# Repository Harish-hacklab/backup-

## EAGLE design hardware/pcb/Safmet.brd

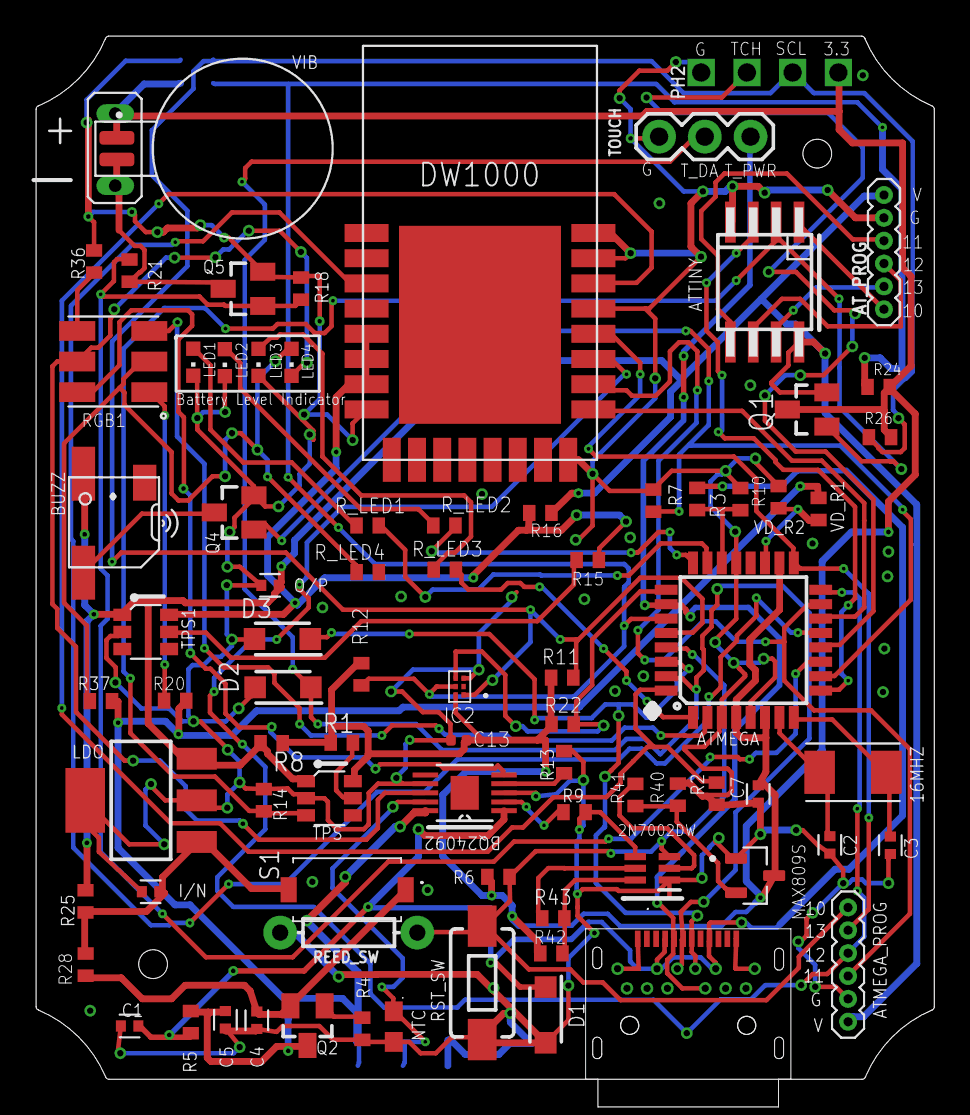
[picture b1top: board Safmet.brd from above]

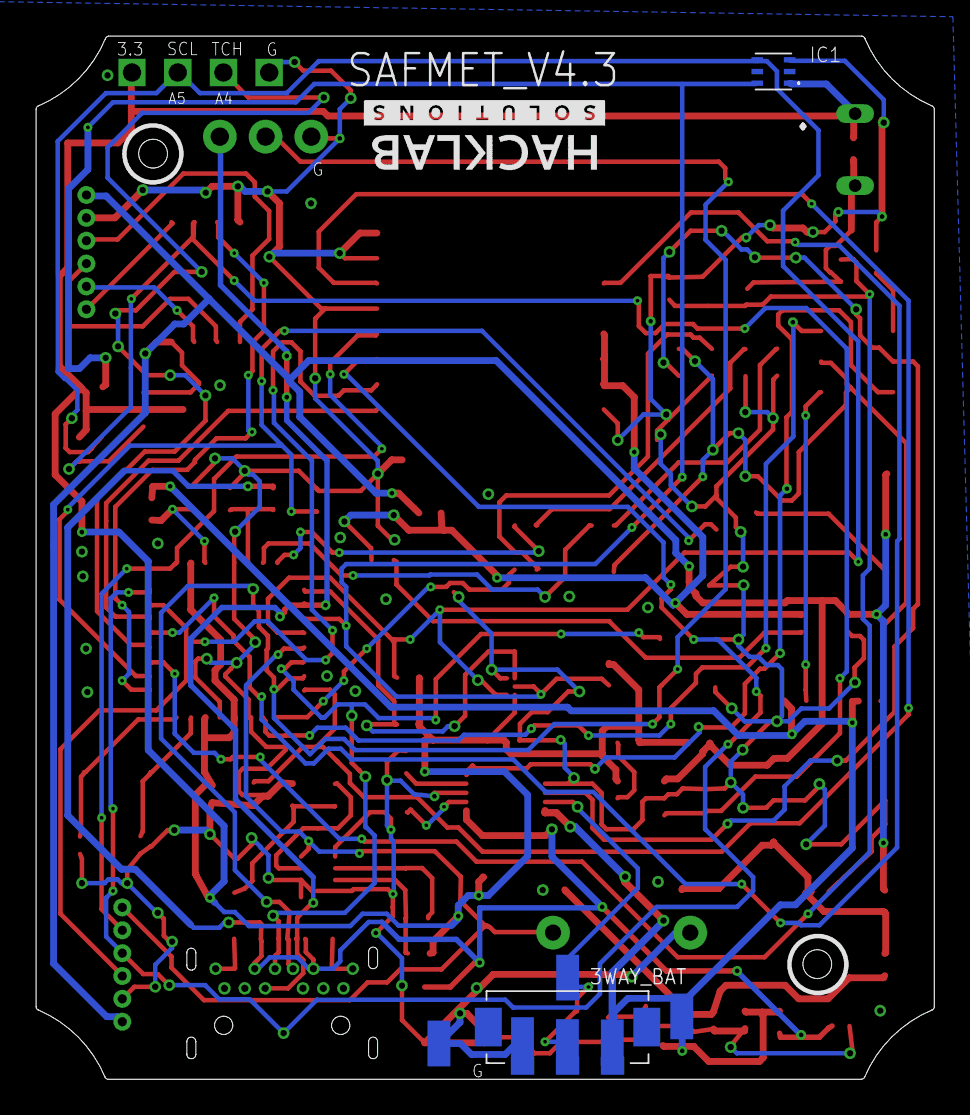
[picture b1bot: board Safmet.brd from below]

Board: 2 copper layers, 49.9 x 58.0 mm, 88 parts (8 on the bottom side), 60 nets.

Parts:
2N7002DW: 2N7002DW; SOT65P210X110-6N
3WAY_BAT: 009155003541006
16MHZ: 16MHz; CRYSTAL-TXC-7A
ATMEGA: ATMEGA328P_TQFP; TQFP32-08
ATMEGA_PROG: 1X06_1.27MM
ATTINY: ATTINY85SU; ATTINY85
AT_PROG: 1X06_1.27MM
BQ24092: BQ24092DGQR; SOP50P490X110-11N
BUZZ: SMT-0540-S-R
C1, C5, C7: 1uF; CAPC1005X60
C2, C3: 18pF; CAPC1005X60
C4: 4.7uF; CAPC1005X60
C13: 1~4.7uF; CAPC1005X55N
D1, D2, D3: SMF5.0CA; SODFL3618X108N
DECAWAVE: DWM1000
I/N: 1uF; CAPC1005X60
IC1: LTR-308ALS-01; LTR303ALS01
IC2: MXC4005XC
LDO: TC1264; SOT223
LED1, LED2, LED3, LED4: CHIPLED_0603
MAX809S: MAX809SN293D3T1G; SOT95P237X111-3N
NTC: NCP18WF104J03RB; THERM_NCP18WF104J03RB
O/P: 1uF 10V; CAPC1005X60
PAD1, PAD2, PAD3, PAD4, PAD5, PAD6: SMD1,27-2,54
PH2: PH1X4-10; PH010-1-4
Q1, Q2: FDN360P; SUPER-SOT3
Q4, Q5: SI2302; SOT23
R1, R14, R15: 1k; R0402
R2, R6, R7, R18, R24, R26: 10K; R0402
R3: 1K; R0402
R4: 10k; R0402
R5, R21, R28: 0; R0402
R8, R16: 0 ohms; R0402
R9: 540; R0402
R10: 2K; R0402
R11, R12, R22: 2.7K; R0402
R13: 4.7k; R0402
R20: 1.5k; R0402
R25: 0ohm; R0402
R36: 220; R0402
R37: 1.5K; R0402
R40: 100k(1%); R0402
R41, R43: 1k(1%); R0402
R42: 10K(1%); R0402
REED_SW: 0; AXIAL-0.3
RGB1: RGBLED5050
RST_SW: MOMENTARY-SWITCH-SPST-SMD-6.0X3.5MM; TACTILE_SWITCH_SMD_6.0X3.5MM
R_LED1, R_LED2, R_LED3, R_LED4: 220; R0402
S1: PTS636_SK50J_SMTR_LFS; PTS636SK50JSMTRLFS
TOUCH: 455-1750-1-ND; 1X03
TPS, TPS1: TPS22918; SOT-23-6
U$1: 2MM; PHLS005-1-2
U$2: 3A_5V; CUI_USB-31C-F-24X7F
VD_R1: 12K; R0402
VD_R2: 3.9K; R0402
VIB: C0720B001F; XDCR_C0720B001F

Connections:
3V3: ATMEGA.4, ATMEGA.6, ATMEGA.18, C7.1, C13.1, IC1.1, IC2.6, MAX809S.3, PH2.4, Q1.3, R1.2, R6.1, R8.1, R11.2, R12.2, R22.2, R24.2, R26.2, R42.1, TPS.VOUT, U$1.2, VIB.1
ADC7: ATMEGA.22, R3.1, R10.2
BUZZ: ATMEGA.10, Q4.1, R7.1
BUZZ-: BUZZ.-, Q4.3
CH_S: BQ24092.8, LED4.C, RGB1.5
DW_3V3: DECAWAVE.VDD3V3, DECAWAVE.VDD3V3.2, DECAWAVE.VDDAON, R15.2, R16.1, TPS1.VOUT
DW_RST: ATMEGA.13, DECAWAVE.RST
GND: 2N7002DW.1, 2N7002DW.4, 3WAY_BAT.3, ATMEGA.3, ATMEGA.5, ATMEGA.21, ATMEGA_PROG.5, ATTINY.4, AT_PROG.5, BQ24092.3, BQ24092.7, C1.2, C2.2, C3.2, C4.1, C5.2, C7.2, C13.2, D1.2, D2.2, D3.2, DECAWAVE.VSS, DECAWAVE.VSS.2, DECAWAVE.VSS.3, DECAWAVE.VSS.4, DECAWAVE.VSS.5, I/N.2, IC1.3, IC2.3, LDO.2, LDO.4, LED1.C, LED2.C, LED3.C, MAX809S.1, NTC.2, O/P.2, PAD2.1, PAD5.1, PH2.1, Q4.2, Q5.2, R2.2, R4.2, R7.2, R9.2, R10.1, R13.1, R14.1, R18.1, R36.1, R40.1, REED_SW.P$1, RST_SW.1, TOUCH.1, TPS.GND, TPS1.GND, VD_R2.2
GPIO: ATMEGA.9, ATTINY.3
IMP_RST: MAX809S.2, R40.2, R41.2
IND: ATMEGA.2, RGB1.3
INT: ATMEGA.32, DECAWAVE.IRQ/GPIO8, R2.1
INT1: ATMEGA.25, IC2.4, R22.1
LED_IND1: ATMEGA.23, R_LED1.2
LED_IND2: ATMEGA.24, R_LED2.2
LED_IND3: ATMEGA.1, R_LED3.2
LS_EN: ATTINY.2, Q1.1, R14.2, TPS.ON
MISO: ATMEGA.16, ATMEGA_PROG.3, DECAWAVE.SPIMISO
MOSI: ATMEGA.15, ATMEGA_PROG.4, DECAWAVE.SPIMOSI
unnamed: 16MHZ.P$2, ATMEGA.8, C3.1
unnamed: 16MHZ.P$1, ATMEGA.7, C2.1
unnamed: 2N7002DW.2, R41.1
unnamed: R1.1, TPS.QOD
unnamed: Q2.1, R4.1
unnamed: LED1.A, R_LED1.1
unnamed: LED2.A, R_LED2.1
unnamed: I/N.1, LDO.1, R25.1, R28.2, S1.2
unnamed: BQ24092.2, R9.1
unnamed: BQ24092.4, R13.2
unnamed: ATMEGA.19, VD_R1.2, VD_R2.1
unnamed: R36.2, RGB1.4
unnamed: R20.1, RGB1.1
unnamed: LED4.A, R37.1, RGB1.2, R_LED4.1
unnamed: R15.1, TPS1.QOD
unnamed: LED3.A, R_LED3.1
unnamed: U$2.A1, U$2.B12
unnamed: U$2.A12, U$2.B1
unnamed: 2N7002DW.6, R42.2, R43.1
unnamed: 2N7002DW.5, R43.2
PB0: ATTINY.5, AT_PROG.4
PB1: ATTINY.6, AT_PROG.3
PB2: ATTINY.7, AT_PROG.2
PB5: ATTINY.1, AT_PROG.1
PG: BQ24092.5, RGB1.6
PWR: BQ24092.1, C1.1, D1.1, R3.2, R5.2, U$2.A4, U$2.A9, U$2.B4, U$2.B9
RST: 2N7002DW.3, ATMEGA.29, ATMEGA_PROG.1, R6.2, REED_SW.P$2, RST_SW.2
RX: ATMEGA.30, D2.1, U$2.A7, U$2.B6
SCK: ATMEGA.17, ATMEGA_PROG.2, DECAWAVE.SPICLK
SCL: ATMEGA.28, IC1.4, IC2.1, PH2.3, R11.1, R26.1
SDA: ATMEGA.27, IC1.6, IC2.5, R12.1, R24.1
SS: ATMEGA.14, DECAWAVE.SPICSN
TH: 3WAY_BAT.2, BQ24092.9, NTC.1, PAD3.1, PAD6.1
TOUCH: ATMEGA.12, PH2.2
TX: ATMEGA.31, D3.1, TOUCH.2, U$2.A6, U$2.B7
T_PWR: ATMEGA.26, TOUCH.3, U$2.A5, U$2.B5
VBAT+: 3WAY_BAT.1, BQ24092.10, C5.1, PAD1.1, PAD4.1, Q2.3, R5.1, R20.2, R37.2, VD_R1.1
VCC: ATMEGA_PROG.6, ATTINY.8, AT_PROG.6, BUZZ.+, LDO.3, O/P.1, Q1.2, R8.2, R16.2, R25.2, TPS.VIN, TPS1.VIN
VIB: ATMEGA.11, Q5.1, R18.2, R21.2
VIB-: Q5.3, R21.1, U$1.1, VIB.2
VLDO: C4.2, Q2.2, R28.1, S1.1

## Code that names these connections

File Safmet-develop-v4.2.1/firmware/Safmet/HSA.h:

/** @file HSA.h
  * @brief This file declares all MACROS, variables and structs */ 



/** @brief GPIO to control Vibration Motor state */
#define VIB_MOTOR 7
/** @brief MACRO defining GPIO connected to ATTINY */
#define ATTINY_GPIO 5 
/** @brief MACRO for DW1000 Load Switch */
#define DW_LS 3
/** @brief ADC Pin used to check Input Power  */
#define PWR_ADC A7       
/** @brief GPIO to check state of TOUCH_SENSOR */
#define TOUCH_SENSOR 8 //TX
/** @brief  using as power supply for touch sensor */
#define T_PWR A3
/** @brief GPIO to control Buzzer state */
#define BUZZER 6

/** @brief GPIO control state of GREEN_LED */
#define GREEN_LED 4
/** @brief GPIO control state of BLUE_LED */
#define BLUE_LED A2 
/** @brief Not used anywhere */
#define CHR_DET 7

/** @brief ADC pin to check battery voltage */
#define VBAT_ADC A6 
#define R1 1.1 //Kohms
#define R2 2.0 //Kohms
#define VD_R1 12.0
#define VD_R2 3.9
#define BAT_LOW_ALERT 3.45// 0.852 for 2.92V, 0.890 for 3.05V,0.845 for 3.45V
#define V_SYS_SLEEP 3.10 //Voltage below which the complete system goes to sleep
byte sleep_counter_led =0;


#define SetupPrint

#define ENABLE true
#define DISABLE false
#define LEN_DATA 100

#define BEACON 0x05

#define max_process_size 3
#define broadcast_address 0xFFFFFFFF

#define ACK 0x01
#define POLL 0x02
#define POLLACK 0x03
#define RANGE 0x04
#define RANGEREPORT 0x05
//#define CONF 0x06
#define CAUTION 0x07
#define BROADCAST 0xFF
#define ERROR_REPORT 0xAF
#define PERCONFIG 0x21
#define TEMPCONFIG 0x29
#define PAYLOADSIZE 20
#define GREATER 1
#define LESSER 0

//Battery Voltage Indicator LEDs
#define LED_IND1 14 
#define LED_IND2 15
#define LED_IND3 3

#define LED1_TH_V 3.45
#define LED2_TH_V 3.75
#define LED3_TH_V 4.05


//Debug code for firmware 4.1.2
#define DEBUG_FW412

DW1000Time rx_time;

uint32_t printtime=0;   ///< Stores time when #check_vbat stores and prints battery voltage
float bat_voltage = 0;  ///< Stores voltage of battery
float volt = 0;   ///< Stores analog reading of #VBAT_ADC * bandgapReference(1.1V)/totalNumberOfSteps(1023)

//32 bit declaration
uint32_t lastBeaconTime = 300; // should not be '0' if so the device will not transmit and keep sleeping

//uint32_t last_indicate = 0;
//uint32_t listen_time = 25;//210 before - listens for ACKS from all CASnodes after transmitting BROADCAST
uint32_t source_uids_array[max_process_size];
uint32_t lastActivity = 0;  ///< `lastActivity` is not checked for anywhere
uint32_t source_UID ;
uint32_t destination_UID;
uint32_t current_active_src_uid;
uint32_t green_led_timer = 0;
uint32_t last_alive = 0;
uint32_t RangingTime = 0;
uint32_t TotalRangingTime = 0;

// 16 bit declarations
float VoltHist[10];
uint32_t green_init=0;
uint32_t VoltHistoryTime = 0;
uint32_t listenModeActiveTime = 0;
uint16_t sleep_timeout = 250; // should be leass than beacon_timeout
uint16_t alarm_timeout = 300; // for access control use 500 not more than that(after this time device goes to sleep to avoid conti communication) //for forklift use 2000
const uint16_t replyDelayTimeUS = 3000;
uint16_t network; ///< Store the Net_ID from received broadcast
uint16_t sub_network ;
uint16_t AckStore_Time = 0; // To check the time between receiving an ACK and completely processing it (storing the ack in source_uids_array[])
uint16_t listen_time = 25; //listens for ACKS from all CASnodes after transmitting BROADCAST
uint16_t BoradcastTimeout_Time = 30; //Goes to Broadcast Timeout Sleep
uint8_t sleep_test = 0;


// 8 bit declaration
byte sid_index = 0;
byte response_count = 0;
uint8_t payload[PAYLOADSIZE]; ///< Stores timestamps of transmission of DW1000
uint8_t packt_id;
static uint8_t  counter = 0;


//byte declaration
byte device_ID[4];//csk
byte data[LEN_DATA];
byte sent_packet_type;
byte packt_type;
byte temp_near;
byte temp_emerg;
byte dist_n_f;
byte dist_e_f;
byte dist_n_f_f;
byte dist_e_f_f;  
byte message[8];
byte BatteryVolts_IND;
//byte LoopDetector_Counter=0;

// float declarations

float distance;

//bool declarations

//bool RangeProcess_Lock = false; //Flag so that ranging process of individual CASnodes are not affected by other CASnodes - if this varaible is used the safmet waits and completes the twr with each casnode before moving to the next one
bool sleep_active = false;
bool beacon;
bool RangeProcess_Flag = false; //To track the TWR Ranging Process
bool CheckFlag = true; // To indicate whether the safemet can execute the check battery and check power functions
bool sleep_act = false;
bool SleepFlag = false; //for Atmega and DW1000 sleep during the working state (TWR)
//boolean InputFlag = false; //SerialInput Check Flag
volatile bool sentAck = false;
volatile bool receivedAck = false;
bool D_ZONE_DETECT = false;
bool enter = false;
bool all_ok = false;


//char[] declaration
//String SerialInput = ""; //Serial Input Buffer

//const declaration

const uint8_t PIN_RST = 9; ///< reset pin
const uint8_t PIN_IRQ = 2; ///< irq pin
const uint8_t PIN_SS = SS; ///< spi select pin

//function declarations
void transmit(uint8_t packt_type, uint8_t pack_id, uint32_t dest_id, uint8_t payload[], uint8_t payload_size);
void gpio_defaults();

void handleSent();
void handleReceived();

void fill_default_transmit();
void receiver();
void handleError();
void handleCaution();
void reInitDeca();
void decawaveInit();
void SerialHandle();
bool check_for_ignore_uid();
void green_setup(){
  green_init = millis;
}
/** @brief This struct stores device ID info */
struct dev_id
{
  uint16_t Net_ID;      ///< 65282 is the net id of 2 bytes used to check whether received packet belongs to the same network or not
  uint16_t Sub_Net_ID;  ///< This 2 bytes informs whether the transmitting device is a helmet or forklift.
  uint32_t Unique_ID;   ///< Each device has 4 byte software generated unique id to verify the responder(destination) has communicated to the respective sender in the complete transmission.
} device;

/** @brief This struct stores list of subnetwork IDs */ 
struct dist
{
  uint32_t dist_SID[5];

} dist_para;

/** @brief This struct stores various parameters related to DW1000 communication */
struct parameter
{
  //byte start = type_en_func;
  uint16_t en_func;//OUT1//OUT2//OUT3//RX-TX//can//i2c//led1//led2//led3//button1//button2//button3
  uint8_t tx_pwr;
  uint8_t rx_pwr;
  uint8_t op_mode;
  uint8_t sleep_time;
  uint8_t wait_time;
  uint16_t beacon_timeout;  ///< The time in milliseconds after which it broadcasts again upon receiving no response
} param;

struct Ignore
{
  uint32_t Ignore_UID[4];
} I_UD;


byte received_packet_type;

DW1000Time timePollSent;
DW1000Time timePollReceived;
DW1000Time timePollAckSent;
DW1000Time timePollAckReceived;
DW1000Time timeRangeSent;       ///< Store the delay after which a DW1000 Range transmission is performed
DW1000Time timeRangeReceived;
// last computed range/time
DW1000Time timeComputedRange;

void reInitDeca()
{
  
  DW1000.reset();
  DW1000.spiWakeup();
  delay(2);
  DW1000.begin(PIN_IRQ, PIN_RST);
  DW1000.select(PIN_SS);
  DW1000.newConfiguration();
  DW1000.setDefaults();
  DW1000.setDeviceAddress(1);
  DW1000.setNetworkId(10);
  DW1000.enableMode(DW1000.MODE_SHORTDATA_FAST_ACCURACY); //MODE_SHORTDATA_FAST_ACCURACY);
  DW1000.commitConfiguration();
  DW1000.attachSentHandler(handleSent);
  DW1000.attachReceivedHandler(handleReceived);
  receiver();

  digitalWrite(ATTINY_GPIO, HIGH);
  delay(1);
  digitalWrite(ATTINY_GPIO, LOW);
  fill_default_transmit();
}

void sendBeaconPacket() {
  if (RangeProcess_Flag == true) //if previously not cleared after rangereport, then clear the flag
  {
    RangeProcess_Flag = false;
  }
  //RangeProcess_Lock = false;

  Serial.println(F("Beacon Timeout Reached"));
  
  gpio_defaults();
  response_count = 0; //delete all the previous acks - source_uids_array will overwrite in the next cycle

#if TOUCH_ENABLE
  if (!checkTouchEnable()) return;
#endif
  packt_id++;
  Serial.println(F("BEACON"));

  //delay(random(0, 50));

  transmit(BROADCAST, packt_id, broadcast_address, payload, 0);
  Serial.println(F("BROADCAST sent"));
  lastBeaconTime = millis();
  listenModeActiveTime = millis();
}

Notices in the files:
parts and their libraries:
SparkFun-FreqCtrl: Licensing: Creative Commons ShareAlike 4.0 International - https://creativecommons.org/licenses/by-sa/4.0
